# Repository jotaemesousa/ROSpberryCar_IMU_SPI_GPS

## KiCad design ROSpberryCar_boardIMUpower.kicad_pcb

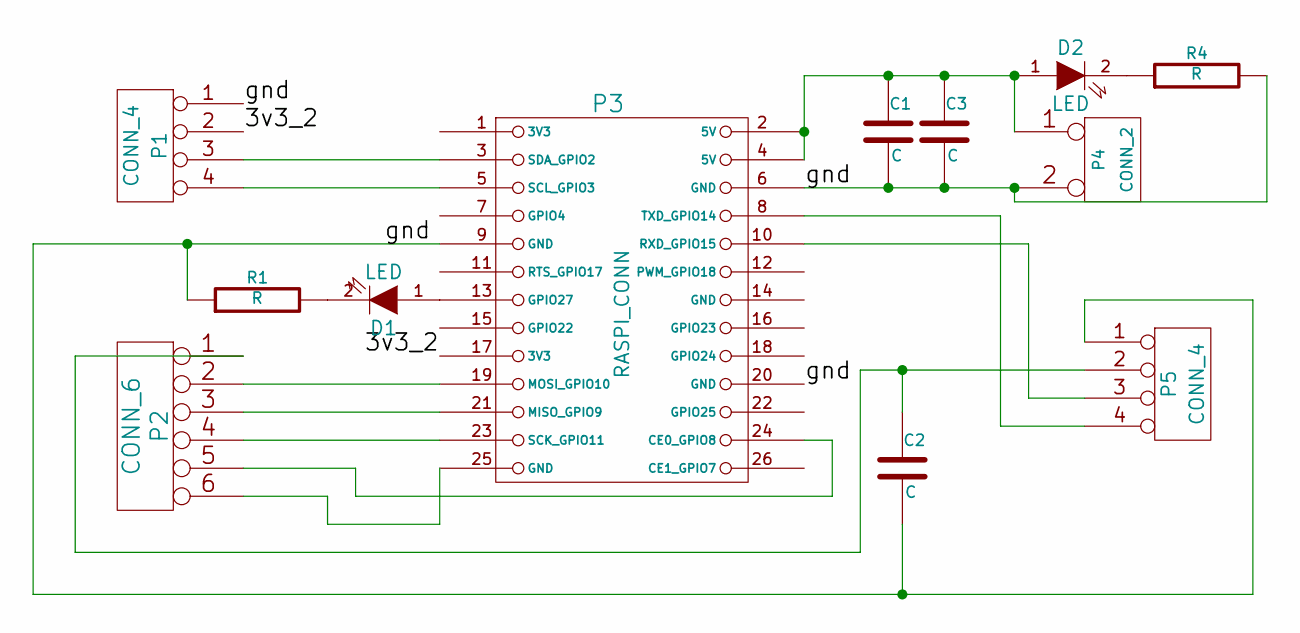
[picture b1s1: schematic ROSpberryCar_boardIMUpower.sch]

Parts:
C1, C2, C3: C
D1, D2: LED
P1, P5: CONN_4
P2: CONN_6
P3: RASPI_CONN
P4: CONN_2
R1, R4: R

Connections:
/3v3_2: P1.2, P3.17 (3V3)
/gnd: C1.2, C2.2, C3.2, P1.1, P3.6 (GND), P3.9 (GND), P3.20 (GND), P4.2 (PM), P5.1, R1.1, R4.2
unnamed: P2.5, P3.24 (CE0_GPIO8)
unnamed: D1.2 (K), R1.2
unnamed: D1.1 (A), P3.13 (GPIO27)
unnamed: P2.6, P3.25 (GND)
unnamed: P3.10 (RXD_GPIO15), P5.3
unnamed: C2.1, P2.1, P5.2
unnamed: P2.3, P3.21 (MISO_GPIO9)
unnamed: P2.2, P3.19 (MOSI_GPIO10)
unnamed: P2.4, P3.23 (SCK_GPIO11)
unnamed: P3.8 (TXD_GPIO14), P5.4
unnamed: P1.4, P3.5 (SCL_GPIO3)
unnamed: P1.3, P3.3 (SDA_GPIO2)
unnamed: D2.2 (K), R4.1
unnamed: C1.1, C3.1, D2.1 (A), P3.2 (5V), P3.4 (5V), P4.1

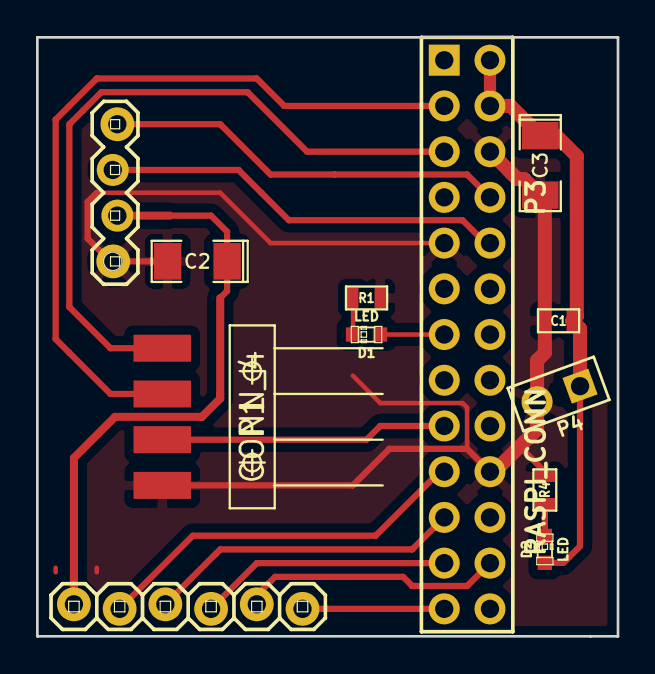
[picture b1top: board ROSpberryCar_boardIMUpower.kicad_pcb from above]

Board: 2 copper layers, 32.3 x 33.3 mm, 12 parts (0 on the bottom side), 16 nets.

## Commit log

2013-11-25 placa feita
2013-12-26 svg exported, added led
2013-12-26 larger pads
2013-12-26 larger pads + svg
